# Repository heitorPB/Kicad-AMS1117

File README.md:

# AMS1117 Voltage Regulator board

Circuit board for AMS1117 low dropout voltage regulator

## Project Files

```
.
├── AMS1117.3dshapes       \\ 3D models of components
├── AMS1117_datasheet.pdf  \\ AMS1117 datasheet
├── AMS1117.kicad_pcb      \\ Board layout
├── AMS1117.lib            \\ Schematic library
├── AMS1117.pretty         \\ Footprints
├── AMS1117.pro            \\ KiCad project
├── AMS1117.sch            \\ Schematic
├── images                 \\ Images
└── README.md              \\ This file
```

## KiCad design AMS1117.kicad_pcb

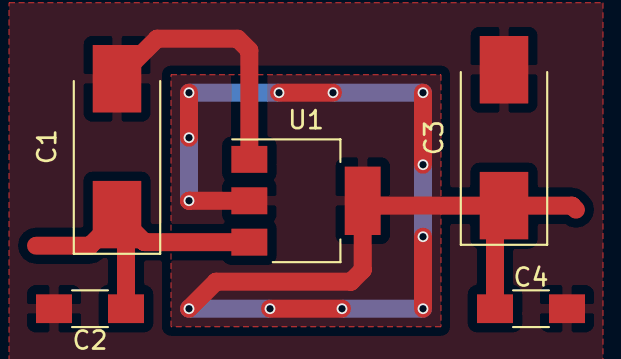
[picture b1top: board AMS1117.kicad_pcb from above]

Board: 2 copper layers, 5 parts (0 on the bottom side), 3 nets.

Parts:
C1: 220 µ; CP_Tantalum_Case-D_EIA-7343-31_Hand
C2, C4: 0.1 µ; C_1206_HandSoldering
C3: 10 µ; CP_Tantalum_Case-D_EIA-7343-31_Hand
U1: AP1117-50; SOT-223-3Lead_TabPin2

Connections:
+5V: C3.1, C4.1, U1.2
+12V: C1.1, C2.1, U1.3
GND: C1.2, C2.2, C3.2, C4.2, U1.1

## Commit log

2017-10-04 Done
